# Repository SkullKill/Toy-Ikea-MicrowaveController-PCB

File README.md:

# Toy-Ikea-MicrowaveController-PCB
PCB for Microwave Controller for Ikea Kitchen DUKTIG

FYI Gerber files are in the release section

https://github.com/SkullKill/Toy-Ikea-MicrowaveController-PCB/releases

  Toy-Ikea-MicrowaveController
  
  Toy Ikea Microwave Controller

  Microware Controller (Arduino Based)
  
  for Ikea Kitchen DUKTIG
  
  LEDBERG LED spotlight
  
  SKaccess by Simon Kong

  www.skaccess.com
  
  ATTiny841

  ------------------------------------------------------------
  ## Features
  
  increment timer by 5 sec from 0 to 60 sec
  
  increment timer by 10 sec from 1min to 5 min
  
  increment timer by 30 sec from 5min onwards to 51min
  
  press the rotary knob to start/pause countdown
  
  light will be on when countdown is active
  
  low tone buzzer noise when counting down to simulate the microwave being on
  
  opening the door while countdown is on will pause countdown
  
  when the door is open, light will be on
  
  when the countdown finishes, will display "End", if the door is not open,
  
    it will do the End melody again every 2 min, untill the door is open.
    
    this is to remind the user that there is still food in the microwave.

  V 1.0 - 30/06/2019 - Initial Release
  ------------------------------------------------------------
  ## PCB Board Used
  
  https://www.skstore.com.au/electronics/pcb/Toy-Ikea-MicrowaveController

  https://github.com/SkullKill/Toy-Ikea-MicrowaveController-PCB

  more pictures in the wiki
  
  https://github.com/SkullKill/Toy-Ikea-MicrowaveController-PCB/wiki
  
  ------------------------------------------------------------
  ## Code Used
  
  https://github.com/SkullKill/Toy-Ikea-MicrowaveController
  
  ------------------------------------------------------------
  ## Video
  
  https://youtu.be/BQZ9P_Z0Fzc

  ------------------------------------------------------------
  ## Product Used (included)
  
  15mm Aluminium Knob
  
  10mm Spacer/Standoff and M3 Screws
  
  ------------------------------------------------------------
  ## Product Used (not included)
  
  - Ikea DUKTIG Play kitchen, birch
  
  Article Number : 403.199.73
  
  https://www.ikea.com/au/en/catalog/products/40319973/

  - Ikea LEDBERG LED spotlight, white, 4 pack
  
  Article Number : 103.517.33
  
  https://www.ikea.com/au/en/catalog/products/10351733/
  
  Note: the cable with the Dark Lines is the -ve/gnd cable. 
  
  But better to double check with a multimeter.

  - magnetic door sensor (reed switch) [could also use a micro switch]
  
  - 3mm Acrylic sheet

  - 50mm L Angle Bracket
  
  https://www.bunnings.com.au/zenith-50mm-zinc-plated-angle-brackets-4-pack_p2760232

  - various screws and bolts 
  
  - 4G X 12mm timber screws
  
  - washer 5/32" / M4
  
  - Bolts & Nuts 3/16" X 15mm / M5

  ------------------------------------------------------------
  Library Used
  
  https://github.com/SpenceKonde/ATTinyCore
  
  https://miguelpynto.github.io/ShiftDisplay/
  
  https://www.pjrc.com/teensy/td_libs_Encoder.html

  ------------------------------------------------------------
  Sketch uses 6850 bytes (90%) of program storage space. Maximum is 7552 bytes.
  Global variables use 226 bytes (44%) of dynamic memory, leaving 286 bytes for local variables. Maximum is 512 bytes.

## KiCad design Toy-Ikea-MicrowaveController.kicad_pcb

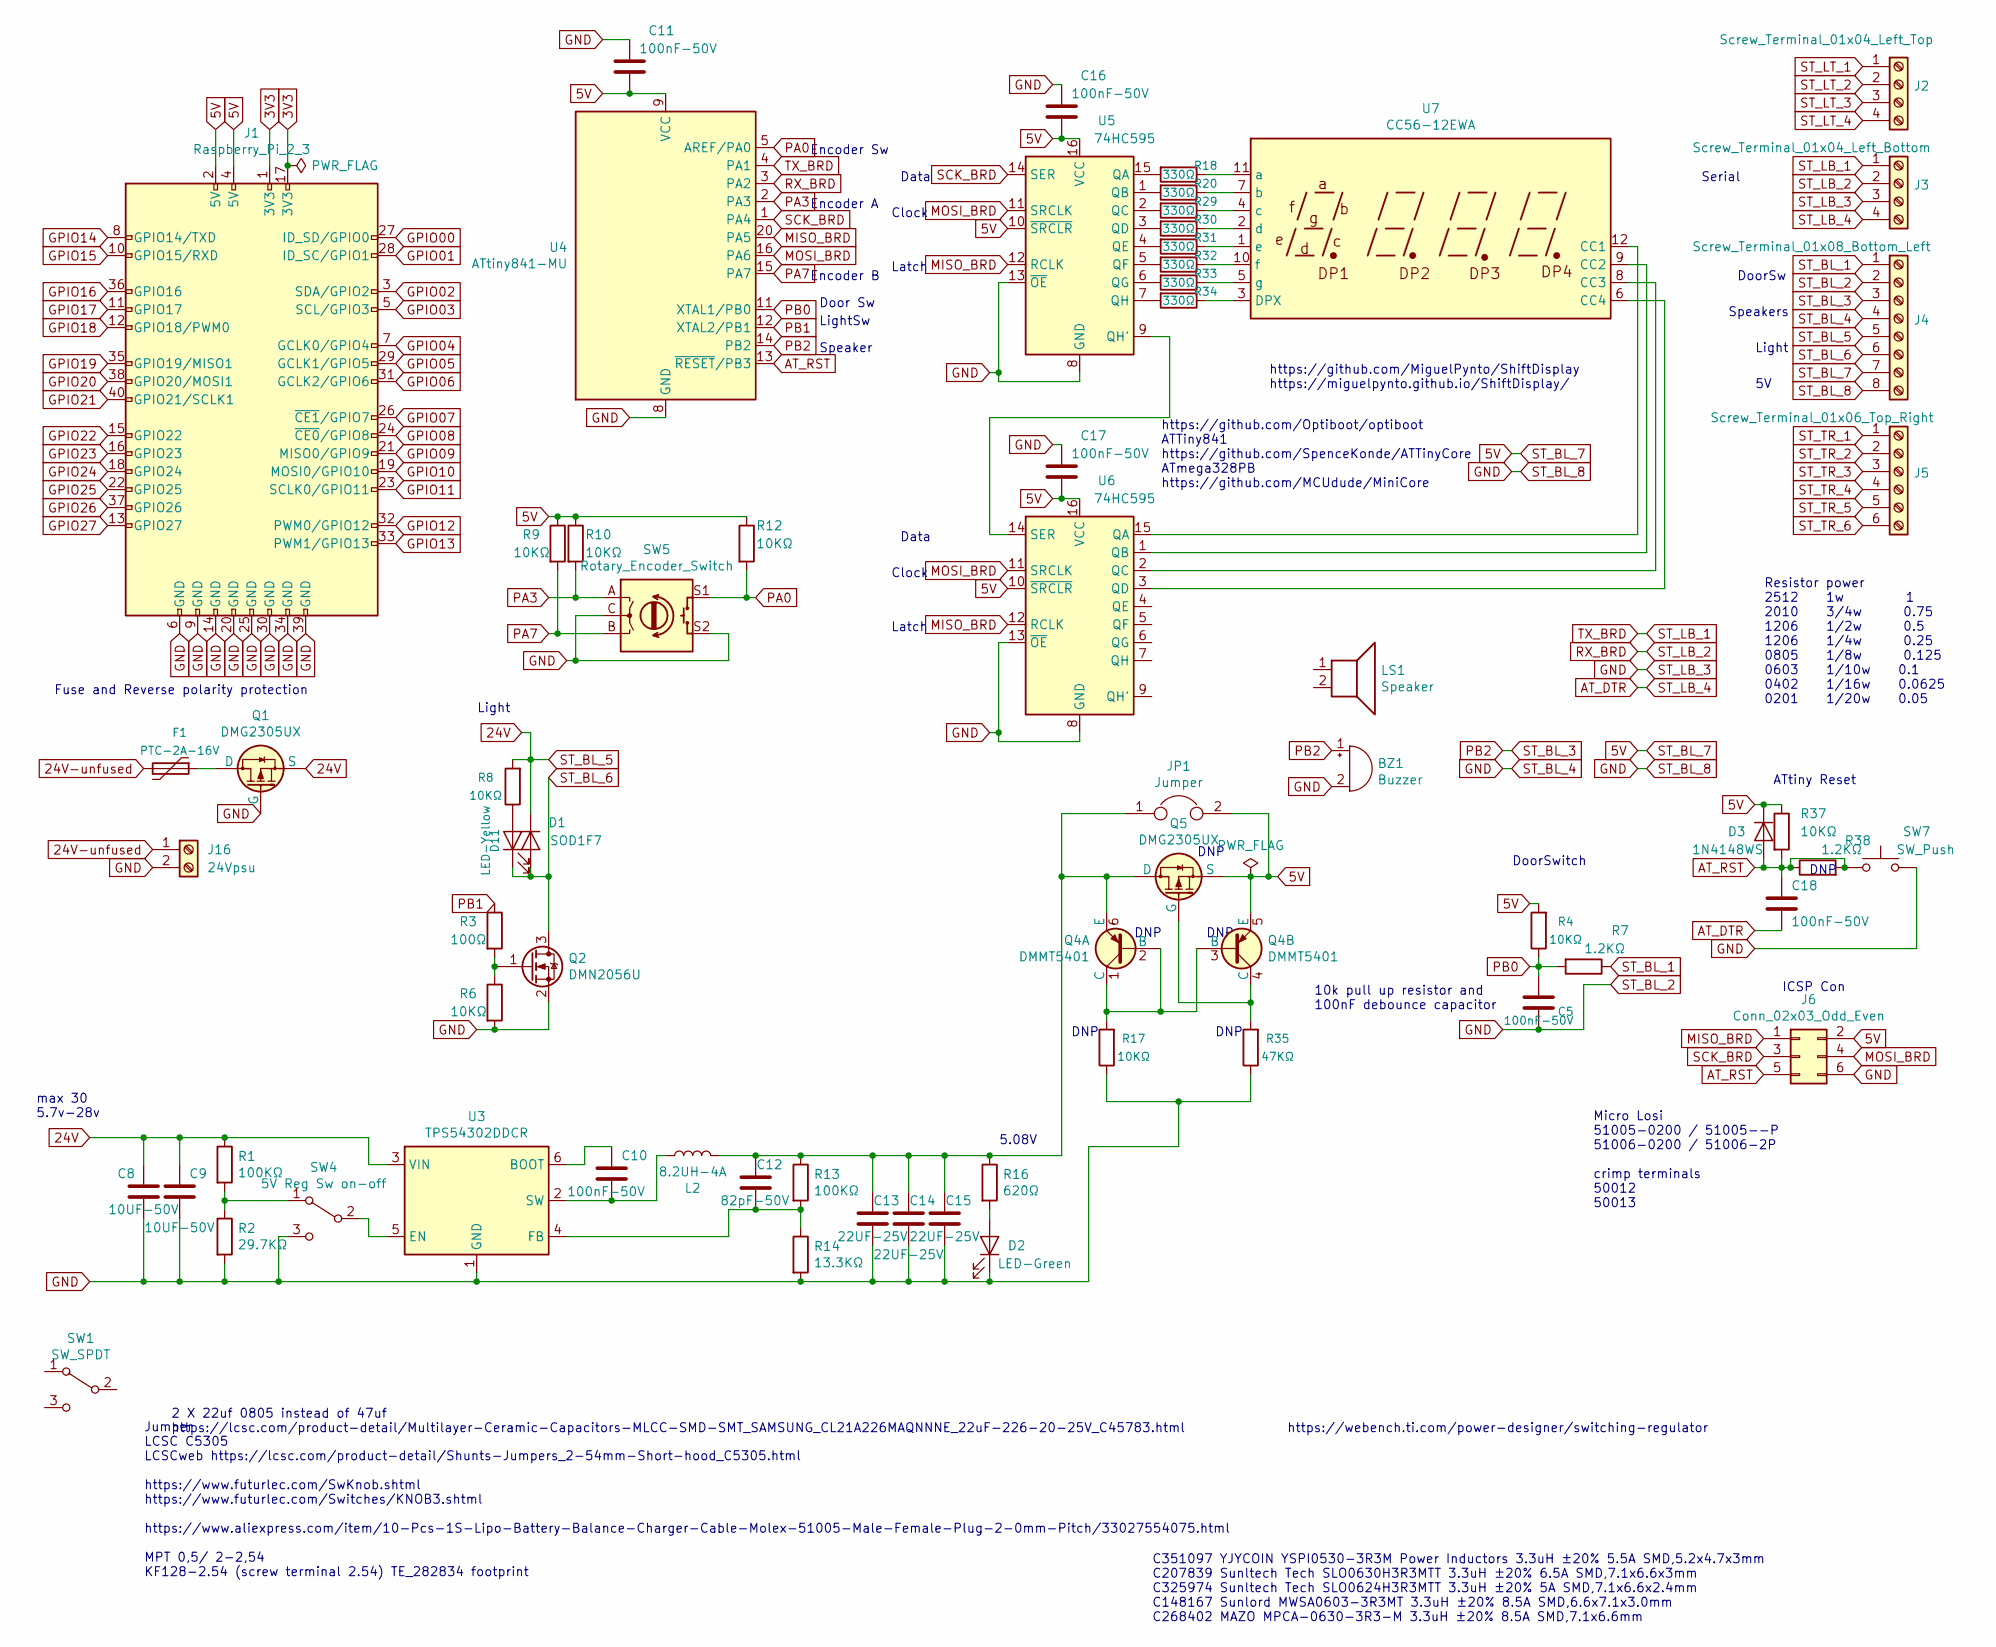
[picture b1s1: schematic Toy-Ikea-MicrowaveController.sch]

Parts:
BZ1: Buzzer; Buzzer_12x9.5RM5.0; MPN ZL-YDW1207-4005PA-5.0; LCSC C219727
C5, C10, C11, C16, C17, C18: 100nF-50V; C_0603_1608Metric; MPN AC0603KRX7R9BB104; LCSC C149620
C8, C9: 10UF-50V; C_1206_3216Metric; MPN CL31A106KBHNNNE; LCSC C13585
C12: 82pF-50V; C_0402_1005Metric; MPN CL05C820JB5NNNC; LCSC C13532
C13, C14, C15: 22UF-25V; C_0805_2012Metric; MPN CL21A226MAQNNNE; LCSC C45783
D1: SOD1F7; D_SOD-123; MPN SOD1F7; LCSC C33221
D2: LED-Green; LED_0603_1608Metric; MPN ORH-G36G; LCSC C205443
D3: 1N4148WS; D_SOD-323; MPN 1N4148WS; LCSC C2128
D11: LED-Yellow; LED_0603_1608Metric; MPN FC-DA1608HYK-588J; LCSC C84268
F1: PTC-2A-16V; Fuse_1812_4532Metric_Pad1.30x3.40mm_HandSolder; MPN SCF200-16-1812R; LCSC C305617
J1: Raspberry_Pi_2_3; PinSocket_2x20_P2.54mm_Vertical; LCSC C50982
J2: Screw_Terminal_01x04_Left_Top; TerminalBlock_TE_282834-4_1x04_P2.54mm_Horizontal; MPN KF128-2.54-4P
J3: Screw_Terminal_01x04_Left_Bottom; TerminalBlock_TE_282834-4_1x04_P2.54mm_Horizontal; MPN KF128-2.54-4P
J4: Screw_Terminal_01x08_Bottom_Left; TerminalBlock_TE_282834-8_1x08_P2.54mm_Horizontal; MPN KF128-2.54-8P
J5: Screw_Terminal_01x06_Top_Right; TerminalBlock_TE_282834-6_1x06_P2.54mm_Horizontal; MPN KF128-2.54-6P
J6: Conn_02x03_Odd_Even; PinHeader_2x03_P2.54mm_Vertical; LCSC C65114
J16: 24Vpsu; TerminalBlock_bornier-2_P5.08mm; MPN WJ126V-5.0-2P; LCSC C8404
JP1: Jumper; PinHeader_1x02_P2.54mm_Vertical; LCSC C124375
L2: 8.2UH-4A; L_6.3x6.3_H3_HandSolder; MPN BCIHP0735-8R2M; LCSC C237933
LS1: Speaker; TerminalBlock_TE_282834-2_1x02_P2.54mm_Horizontal; LCSC C391012
Q1, Q5: DMG2305UX; SOT-23; MPN DMG2305UX-13; LCSC C144153
Q2: DMN2056U; SOT-23; MPN DMN2056U-7; LCSC C332302
Q4: DMMT5401; SOT-23-6; MPN DMMT5401-7-F; LCSC C154733
R1: 100KΩ; R_0603_1608Metric; MPN RC0603FR-07100KL; LCSC C14675
R2: 29.7KΩ; R_0603_1608Metric; MPN RC0603FR-0729K4L; LCSC C137752
R3: 100Ω; R_0603_1608Metric; MPN RC0603FR-07100RL; LCSC C105588
R4, R6, R8, R9, R10, R12, R17, R37: 10KΩ; R_0603_1608Metric; MPN RC0603FR-0710KL; LCSC C98220
R7, R38: 1.2KΩ; R_0603_1608Metric; MPN RC0603FR-071K2L; LCSC C114605
R13: 100KΩ; R_0603_1608Metric; MPN RTT031003FTP; LCSC C103200
R14: 13.3KΩ; R_0603_1608Metric; MPN RC0603FR-0713K3L; LCSC C185373
R16: 620Ω; R_0603_1608Metric; MPN RTT036200FTP; LCSC C103749
R18, R20, R29, R30, R31, R32, R33, R34: 330Ω; R_0603_1608Metric; MPN RC0603FR-07330RL; LCSC C105881
R35: 47KΩ; R_0603_1608Metric; MPN AC0603FR-0747KL; LCSC C111134
SW1: SW_SPDT; SW_CuK_OS102011MA1QN1_SPDT_Angled; MPN SK-12D02-VG5; LCSC C136722
SW4: 5V Reg Sw on-off; SW_SPDT_PCM12; MPN K3-1296S-E2; LCSC C136659
SW5: Rotary_Encoder_Switch; RotaryEncoder_Alps_EC11E-Switch_Vertical_H20mm; MPN EC11E1834403; LCSC C361165
SW7: SW_Push; SW_SPST_TL3305A; LCSC C174049
U3: TPS54302DDCR; SOT-23-6; MPN TPS54302DDCR; LCSC C311983
U4: ATtiny841-MU; QFN-20-1EP_4x4mm_P0.5mm_EP2.6x2.6mm; MPN ATTINY841-MU
U5, U6: 74HC595; SOIC-16_3.9x9.9mm_P1.27mm; MPN 74HC595D,118; LCSC C5947
U7: CC56-12EWA; CA56-12EWA; LCSC C10709

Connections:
3V3: J1.1 (3V3), J1.17 (3V3)
5V: C11.2, C16.2, C17.2, D3.1 (K), J1.2 (5V), J1.4 (5V), J4.7, J6.2, JP1.2, Q4.5 (E), Q5.2 (S), R4.2, R9.1, R10.1, R12.1, R37.1, U4.9 (VCC), U5.10 (~SRCLR), U5.16 (VCC), U6.10 (~SRCLR), U6.16 (VCC)
24V: C8.1, C9.1, D1.1 (K), J4.5, Q1.2 (S), R1.1, R8.2, U3.3 (VIN)
24V-unfused: F1.2, J16.1
AT_DTR: C18.2, J3.4
AT_RST: C18.1, D3.2 (A), J6.5, R37.2, R38.1, R38.2, SW7.1, U4.13 (~RESET~/PB3)
GND: BZ1.2 (+), C5.2, C8.2, C9.2, C11.1, C13.2, C14.2, C15.2, C16.1, C17.1, D2.1 (K), J1.6 (GND), J1.9 (GND), J1.14 (GND), J1.20 (GND), J1.25 (GND), J1.30 (GND), J1.34 (GND), J1.39 (GND), J3.3, J4.2, J4.4, J4.8, J6.6, J16.2, Q1.1 (G), Q2.2 (S), R2.2, R6.2, R14.2, R17.1, R35.1, SW4.3 (C), SW5.C, SW5.S2, SW7.2, U3.1 (GND), U4.8 (GND), U4.21 (GND), U5.8 (GND), U5.13 (~OE), U6.8 (GND), U6.13 (~OE)
GPIO00: J1.27 (ID_SD/GPIO0)
GPIO01: J1.28 (ID_SC/GPIO1)
GPIO02: J1.3 (SDA/GPIO2)
GPIO03: J1.5 (SCL/GPIO3)
GPIO04: J1.7 (GCLK0/GPIO4)
GPIO05: J1.29 (GCLK1/GPIO5)
GPIO06: J1.31 (GCLK2/GPIO6)
GPIO07: J1.26 (~CE1~/GPIO7)
GPIO08: J1.24 (~CE0~/GPIO8)
GPIO09: J1.21 (MISO0/GPIO9)
GPIO10: J1.19 (MOSI0/GPIO10)
GPIO11: J1.23 (SCLK0/GPIO11)
GPIO12: J1.32 (PWM0/GPIO12)
GPIO13: J1.33 (PWM1/GPIO13)
GPIO14: J1.8 (GPIO14/TXD)
GPIO15: J1.10 (GPIO15/RXD)
GPIO16: J1.36 (GPIO16)
GPIO17: J1.11 (GPIO17)
GPIO18: J1.12 (GPIO18/PWM0)
GPIO19: J1.35 (GPIO19/MISO1)
GPIO20: J1.38 (GPIO20/MOSI1)
GPIO21: J1.40 (GPIO21/SCLK1)
GPIO22: J1.15 (GPIO22)
GPIO23: J1.16 (GPIO23)
GPIO24: J1.18 (GPIO24)
GPIO25: J1.22 (GPIO25)
GPIO26: J1.37 (GPIO26)
GPIO27: J1.13 (GPIO27)
MISO_BRD: J6.1, U4.20 (PA5), U5.12 (RCLK), U6.12 (RCLK)
MOSI_BRD: J6.4, U4.16 (PA6), U5.11 (SRCLK), U6.11 (SRCLK)
unnamed: C10.1, U3.6 (BOOT)
unnamed: C10.2, L2.1, U3.2 (SW)
unnamed: C12.1, C13.1, C14.1, C15.1, JP1.1, L2.2, Q4.6 (E), Q5.3 (D), R13.1, R16.1
unnamed: C12.2, R13.2, R14.1, U3.4 (FB)
unnamed: D2.2 (A), R16.2
unnamed: D11.2 (A), R8.1
unnamed: F1.1, Q1.3 (D)
unnamed: Q2.1 (G), R3.2, R6.1
unnamed: Q4.1 (C), Q4.2 (B), Q4.3 (B), R17.2
unnamed: Q4.4 (C), Q5.1 (G), R35.2
unnamed: R1.2, R2.1, SW4.1 (A)
unnamed: R18.1, U7.11 (a)
unnamed: R18.2, U5.15 (QA)
unnamed: R20.1, U7.7 (b)
unnamed: R20.2, U5.1 (QB)
unnamed: R29.1, U7.4 (c)
unnamed: R29.2, U5.2 (QC)
unnamed: R30.1, U7.2 (d)
unnamed: R30.2, U5.3 (QD)
unnamed: R31.1, U7.1 (e)
unnamed: R31.2, U5.4 (QE)
unnamed: R32.1, U7.10 (f)
unnamed: R32.2, U5.5 (QF)
unnamed: R33.1, U7.5 (g)
unnamed: R33.2, U5.6 (QG)
unnamed: R34.1, U7.3 (DPX)
unnamed: R34.2, U5.7 (QH)
unnamed: SW4.2 (B), U3.5 (EN)
unnamed: U5.9 (QH'), U6.14 (SER)
unnamed: U6.1 (QB), U7.9 (CC2)
unnamed: U6.2 (QC), U7.8 (CC3)
unnamed: U6.3 (QD), U7.6 (CC4)
unnamed: U6.15 (QA), U7.12 (CC1)
PA0: R12.2, SW5.S1, U4.5 (AREF/PA0)
PA3: R10.2, SW5.A, U4.2 (PA3)
PA7: R9.2, SW5.B, U4.15 (PA7)
PB0: C5.1, R4.1, R7.2, U4.11 (XTAL1/PB0)
PB1: R3.1, U4.12 (XTAL2/PB1)
PB2: BZ1.1 (-), J4.3, U4.14 (PB2)
RX_BRD: J3.2, U4.3 (PA2)
SCK_BRD: J6.3, U4.1 (PA4), U5.14 (SER)
ST_BL_1: J4.1, R7.1
ST_BL_6: D1.2 (A), D11.1 (K), J4.6, Q2.3 (D)
ST_LB_1: J3.1, U4.4 (PA1)
ST_TR_1: J5.1
ST_TR_2: J5.2
ST_TR_3: J5.3
ST_TR_4: J5.4
ST_TR_5: J5.5
ST_TR_6: J5.6

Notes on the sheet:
https://webench.ti.com/power-designer/switching-regulator
10k pull up resistor and 100nF debounce capacitor
Jumper LCSC C5305 LCSCweb https://lcsc.com/product-detail/Shunts-Jumpers_2-54mm-Short-hood_C5305.html https://www.futurlec.com/SwKnob.shtml https://www.futurlec.com/Switches/KNOB3.shtml https://www.aliexpress.com/item/10-Pcs-1S-Lipo-Battery-Balance-Charger-Cable-Molex-51005-Male-Female-Plug-2-0mm-P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
2 X 22uf 0805 instead of 47uf https://lcsc.com/product-detail/Multilayer-Ceramic-Capacitors-MLCC-SMD-SMT_SAMSUNG_CL21A226MAQNNNE_22uF-226-20-25V_C45783.html
C351097 YJYCOIN YSPI0530-3R3M Power Inductors 3.3uH ±20% 5.5A SMD,5.2x4.7x3mm C207839 Sunltech Tech SLO0630H3R3MTT 3.3uH ±20% 6.5A SMD,7.1x6.6x3mm C325974 Sunltech Tech SLO0624H3R3MTT 3.3uH ±20% 5A SMD,7.1x6.6x2.4mm C148167 Sunlord MWSA0603-3R3MT 3.3uH ±20% 8.5A SMD,6.6x7.1x3.0mm C268402 MAZO MPCA-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
Fuse and Reverse polarity protection
Resistor power 2512 1w 1 2010 3/4w 0.75 1206 1/2w 0.5 1206 1/4w 0.25 0805 1/8w 0.125 0603 1/10w 0.1 0402 1/16w 0.0625 0201 1/20w 0.05
Micro Losi 51005-0200 / 51005--P 51006-0200 / 51006-2P crimp terminals 50012 50013
5.08V
ATtiny Reset
ICSP Con
Clock
Latch
Data
https://github.com/MiguelPynto/ShiftDisplay https://miguelpynto.github.io/ShiftDisplay/
Light
Speakers
DoorSw
Serial
Encoder A
Encoder B
Encoder Sw
Speaker
Door Sw
LightSw
DoorSwitch
https://github.com/Optiboot/optiboot ATTiny841 https://github.com/SpenceKonde/ATTinyCore ATmega328PB https://github.com/MCUdude/MiniCore
max 30 5.7v-28v
DNP

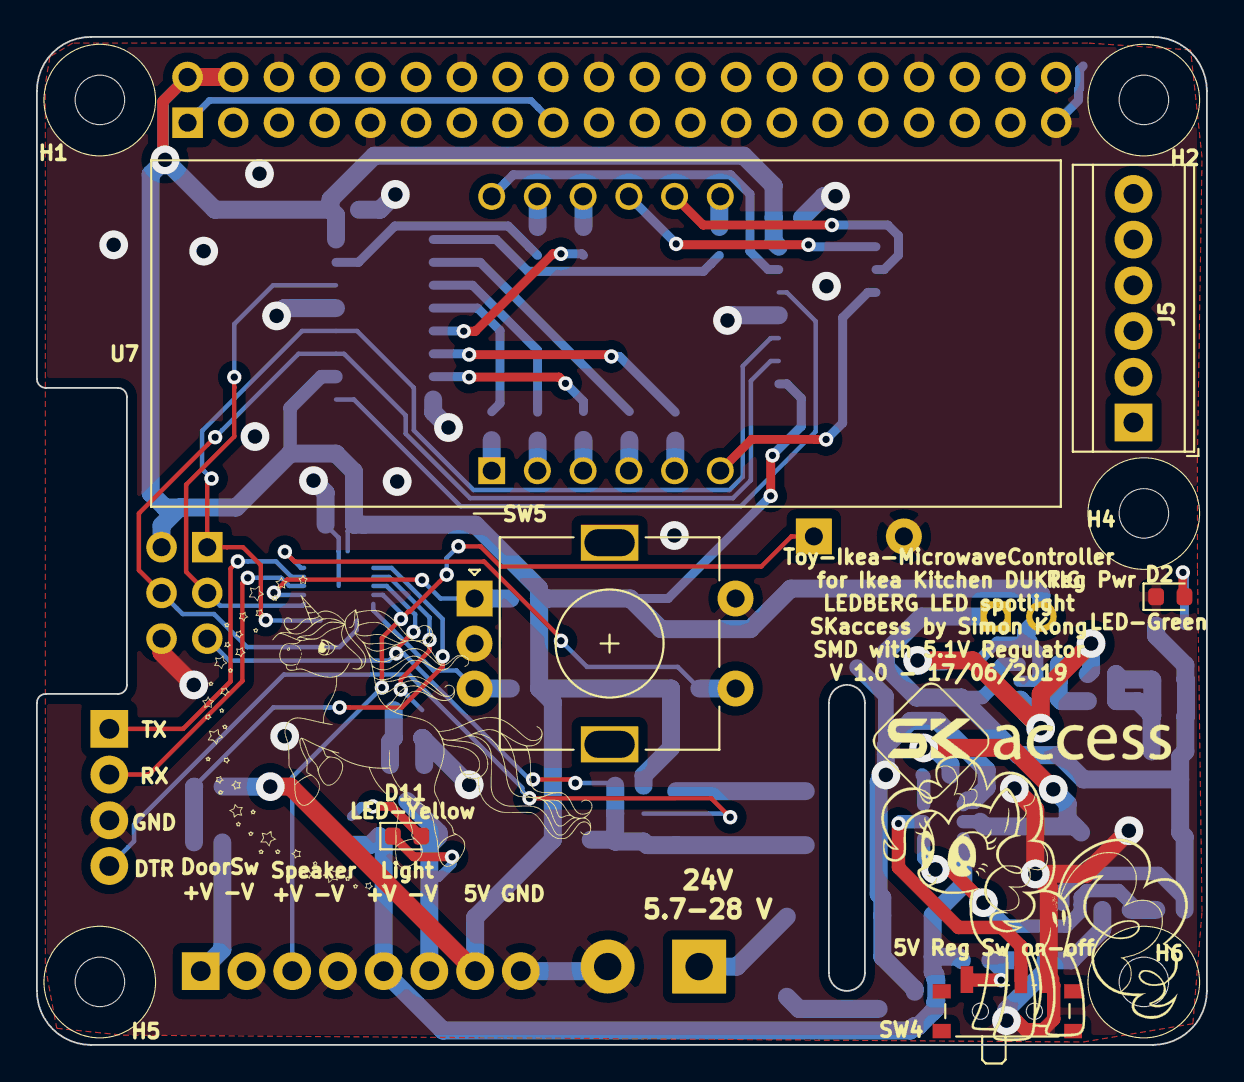
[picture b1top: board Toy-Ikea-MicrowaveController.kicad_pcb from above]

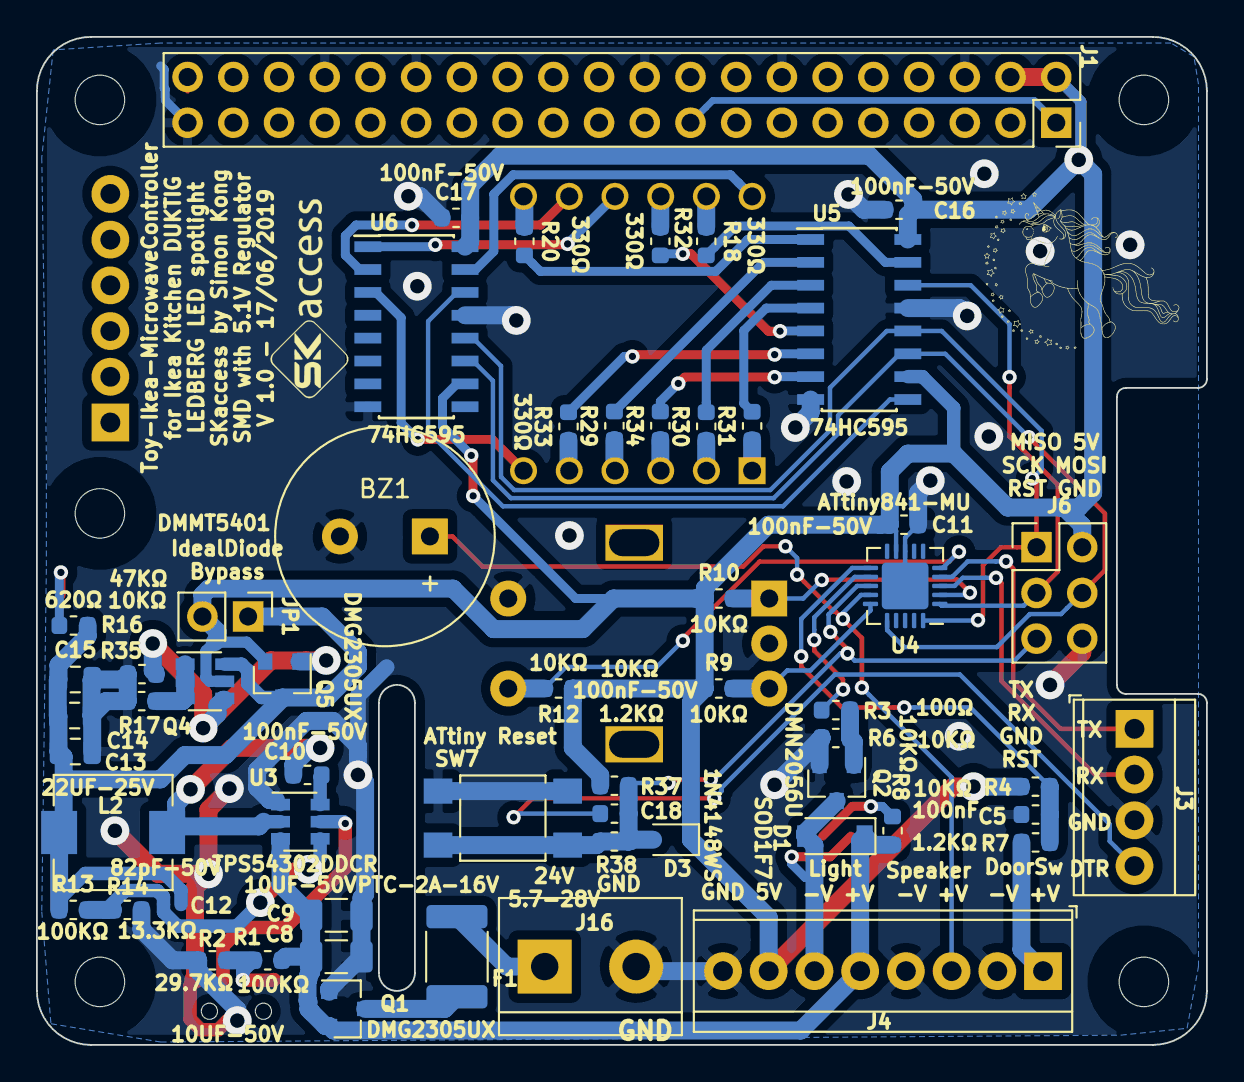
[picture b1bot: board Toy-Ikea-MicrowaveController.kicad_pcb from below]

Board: 2 copper layers, 65.0 x 56.0 mm, 68 parts (57 on the bottom side), 53 nets.

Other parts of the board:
H1, H2, H4, H5, H6: MountingHole; MountingHole_2.75mm_M2.5_NoPad

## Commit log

2019-07-05 Create test
2019-07-05 initial
2019-07-05 updated link for gerber files
